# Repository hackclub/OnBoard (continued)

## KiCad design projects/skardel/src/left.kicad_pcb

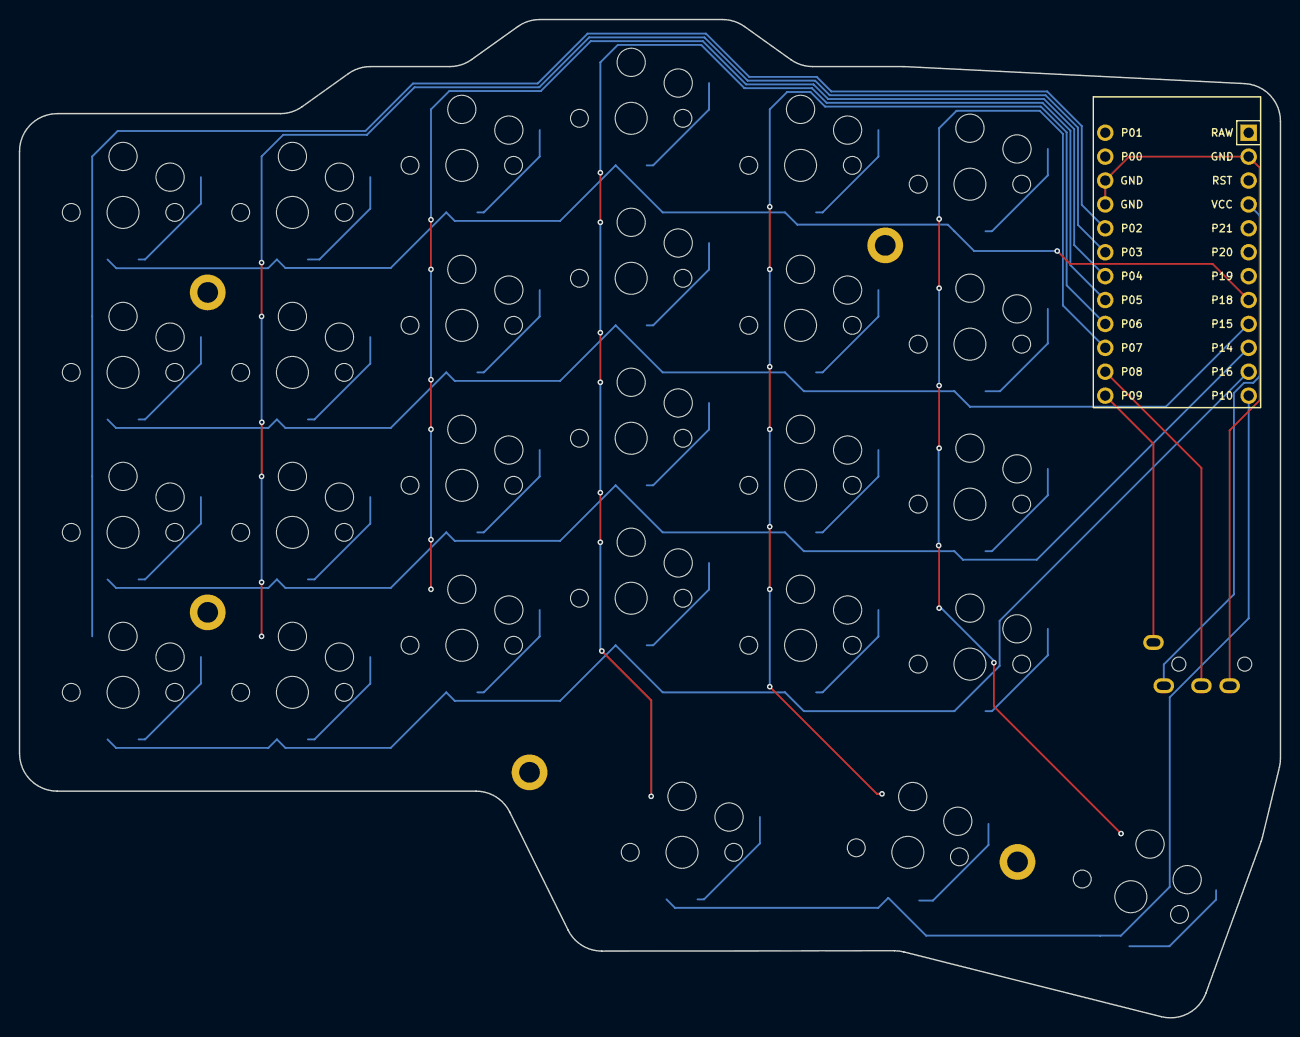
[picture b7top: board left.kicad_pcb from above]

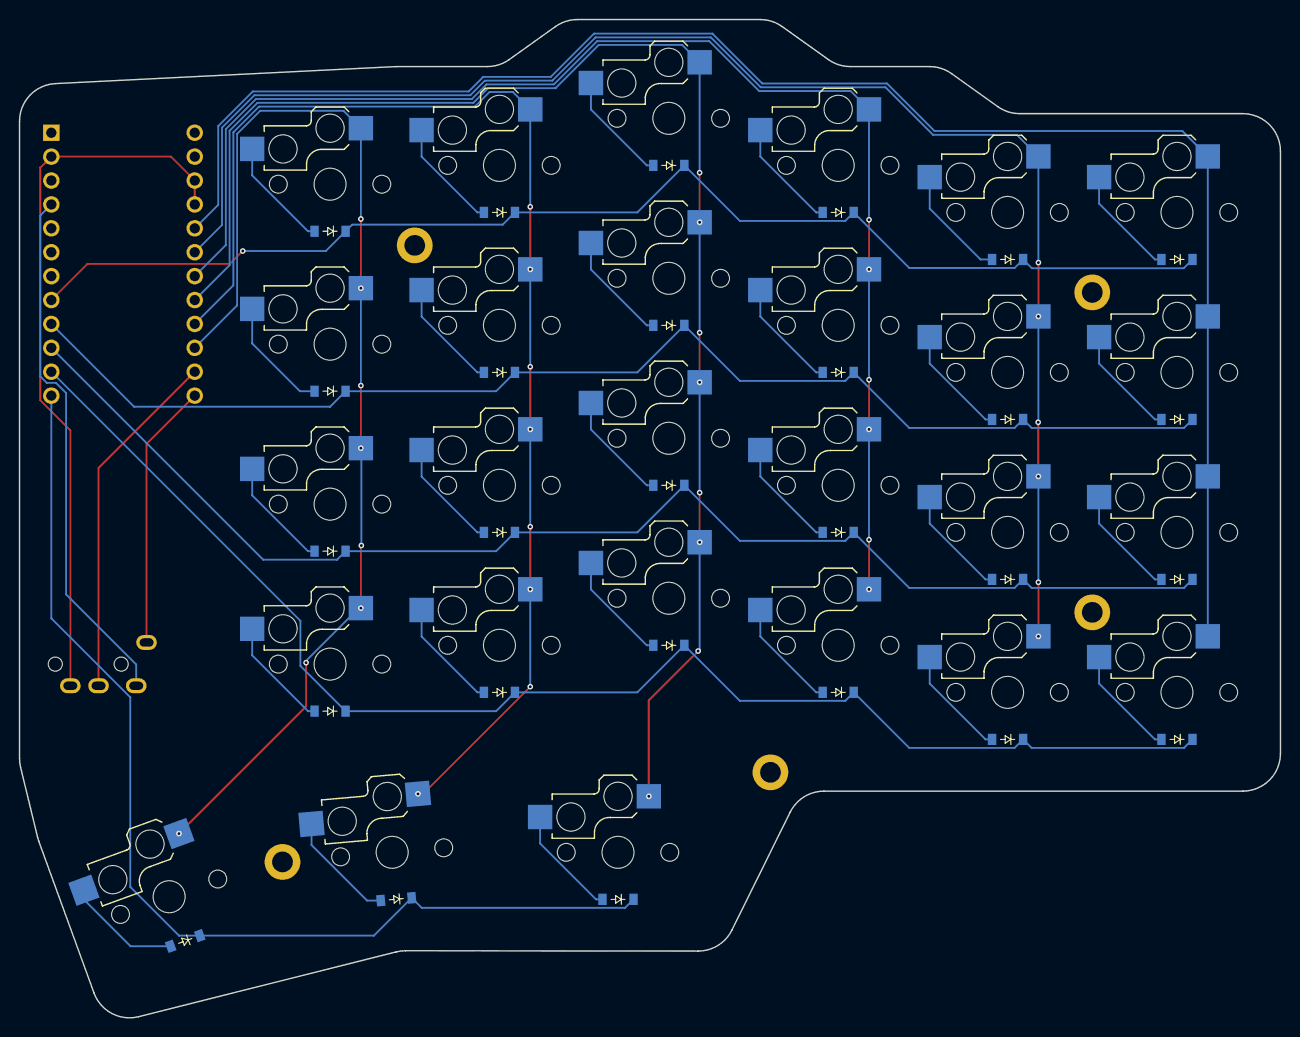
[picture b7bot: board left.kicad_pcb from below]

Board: 2 copper layers, 134.0 x 106.1 mm, 61 parts (54 on the bottom side), 42 nets.

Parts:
D1, D2, D3, D4, D5, D6, D7, D8, D9, D10, D11, D12, D13, D14, D15, D16, D17, D18, D19, D20, D21, D22, D23, D24, D25, D26, D27: diode_tht_sod123
H1, H2, H3, H4, H5: mounting_hole_plated
MCU1: ProMicro
S1, S2, S3, S4, S5, S6, S7, S8, S9, S10, S11, S12, S13, S14, S15, S16, S17, S18, S19, S20, S21, S22, S23, S24, S25, S26, S27: switch_choc_v1_v2
TRRS1: trrs_pj320a

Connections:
GND: MCU1.2, MCU1.15, MCU1.16, TRRS1.2
P2: MCU1.17, S1.1, S2.1, S3.1, S4.1
P3: MCU1.18, S5.1, S6.1, S7.1, S8.1
P4: MCU1.19, S9.1, S10.1, S11.1, S12.1
P5: MCU1.20, S13.1, S14.1, S15.1, S16.1, S25.1
P6: MCU1.21, S17.1, S18.1, S19.1, S20.1, S26.1
P7: MCU1.22, S21.1, S22.1, S23.1, S24.1, S27.1
P8: MCU1.23, TRRS1.3
P9: MCU1.24, TRRS1.5
P10: D25.1, D26.1, D27.1, MCU1.12
P14: D2.1, D6.1, D10.1, D14.1, D18.1, D22.1, MCU1.10
P15: D3.1, D7.1, D11.1, D15.1, D19.1, D23.1, MCU1.9
P16: D1.1, D5.1, D9.1, D13.1, D17.1, D21.1, MCU1.11
P18: D4.1, D8.1, D12.1, D16.1, D20.1, D24.1, MCU1.8
VCC: MCU1.4, TRRS1.4
home_home: D26.2, S26.2
in_home: D27.2, S27.2
index_bottom: D17.2, S17.2
index_home: D18.2, S18.2
index_num: D20.2, S20.2
index_top: D19.2, S19.2
inner_bottom: D21.2, S21.2
inner_home: D22.2, S22.2
inner_num: D24.2, S24.2
inner_top: D23.2, S23.2
middle_bottom: D13.2, S13.2
middle_home: D14.2, S14.2
middle_num: D16.2, S16.2
middle_top: D15.2, S15.2
out_home: D25.2, S25.2
outer_bottom: D1.2, S1.2
outer_home: D2.2, S2.2
outer_num: D4.2, S4.2
outer_top: D3.2, S3.2
pinky_bottom: D5.2, S5.2
pinky_home: D6.2, S6.2
pinky_num: D8.2, S8.2
pinky_top: D7.2, S7.2
ring_bottom: D9.2, S9.2
ring_home: D10.2, S10.2
ring_num: D12.2, S12.2
ring_top: D11.2, S11.2
